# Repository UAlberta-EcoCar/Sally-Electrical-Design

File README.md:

# Branch for the original FOC-BOARD

Source code is located inside V1/FOC_SRC_V1
This is a CMake based project, and should be able to run in `STM32CubeIDE` or `STM32CubeIDE for VSCode`.

## Setup (If using Make)
1. Move inside V1/FOC_SRC_V1
```bash
cd V1/FOC_SRC_V1
```
2. Run the setup script
```bash
bash setup.sh
```
3. Run makefile to flash to device
```bash
make all
make flash
```

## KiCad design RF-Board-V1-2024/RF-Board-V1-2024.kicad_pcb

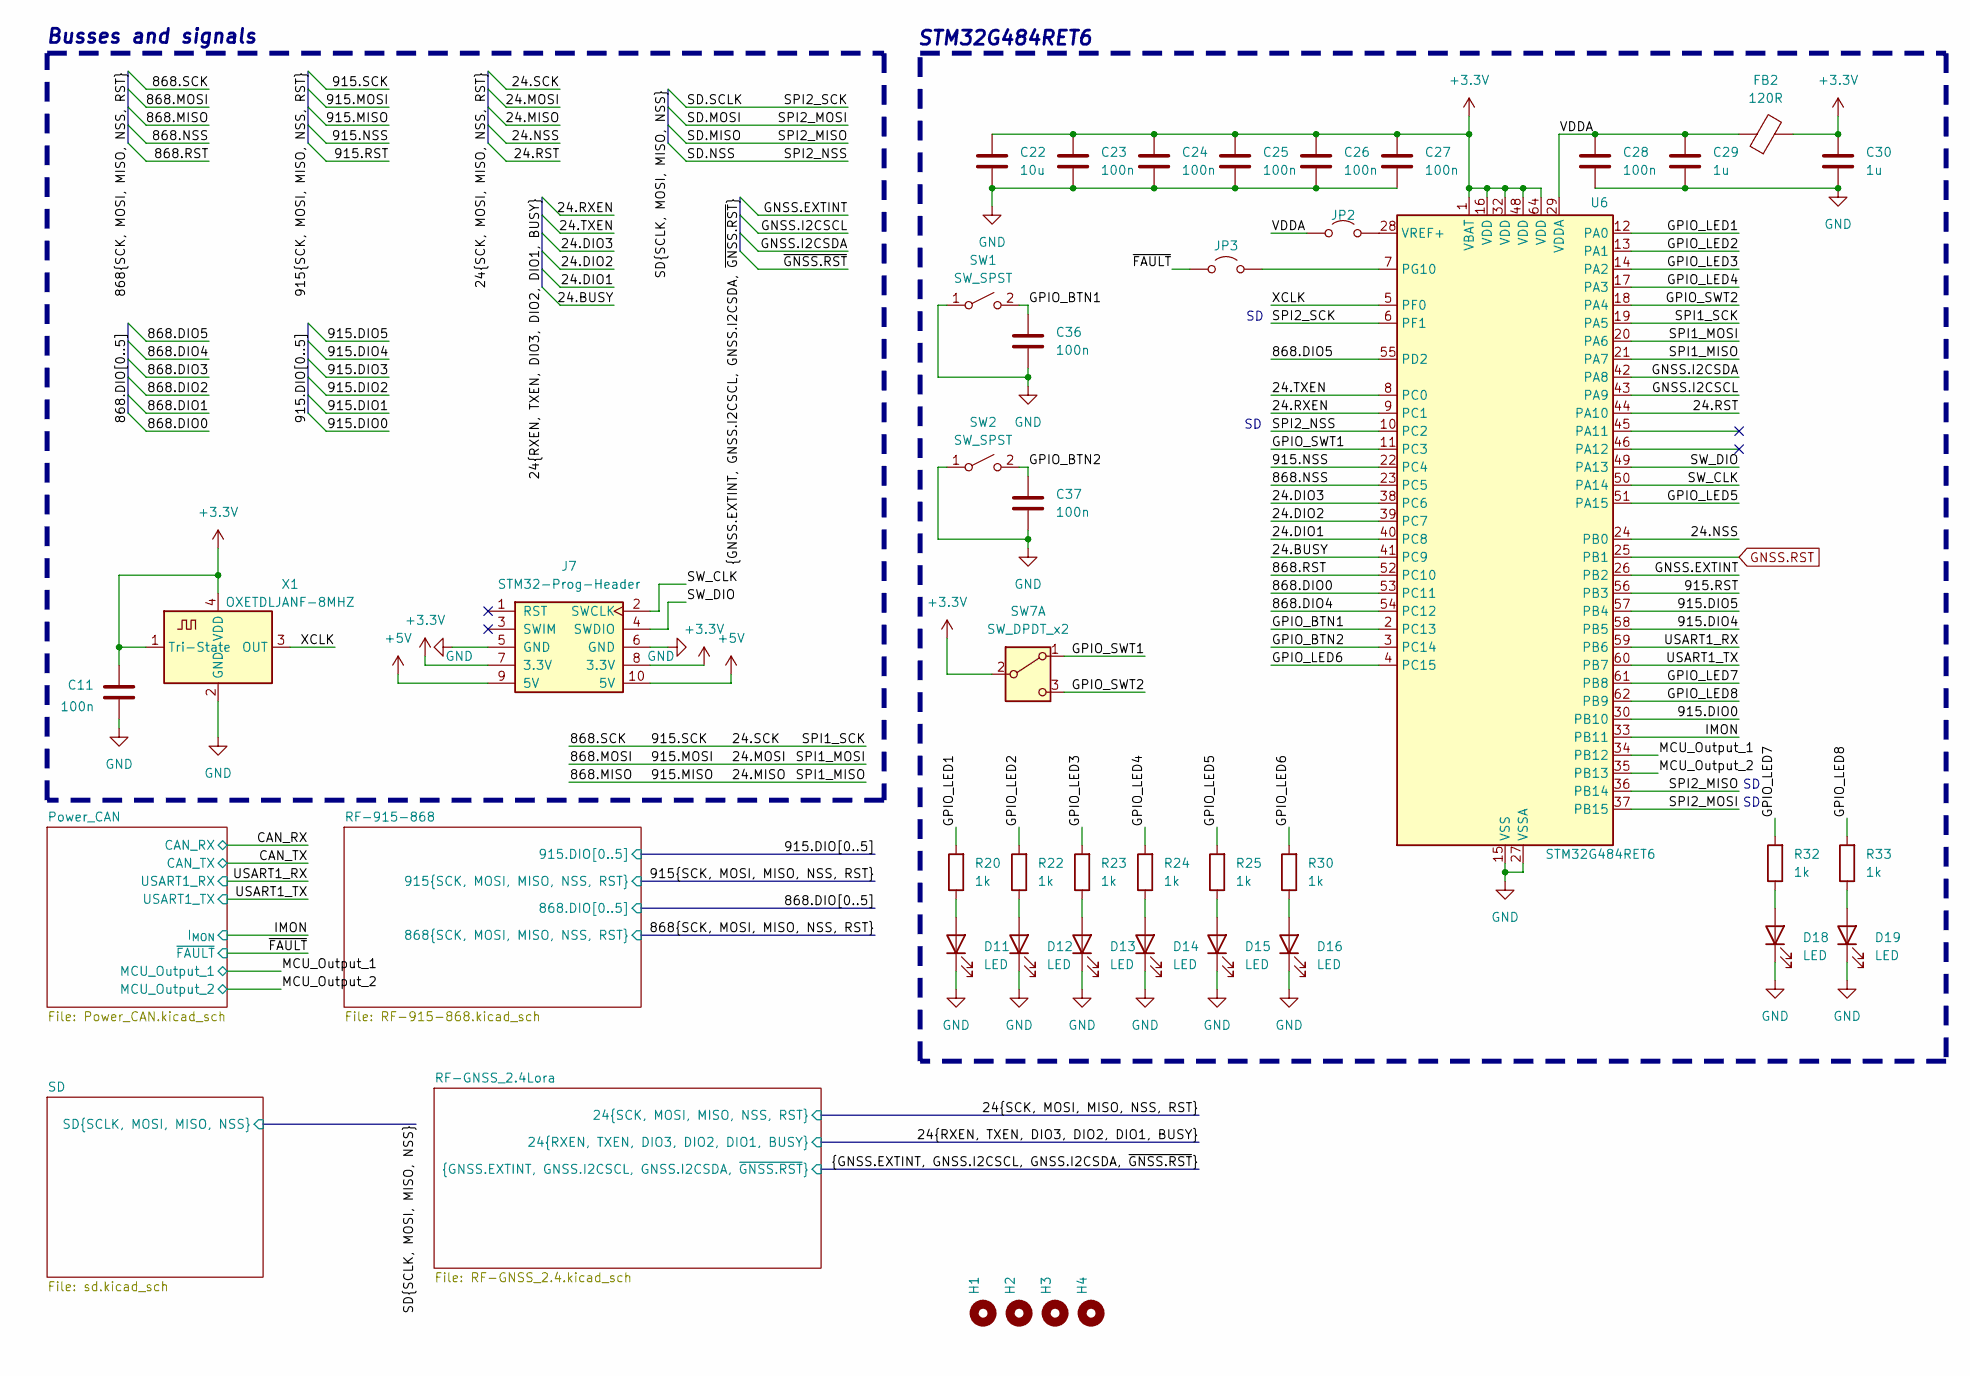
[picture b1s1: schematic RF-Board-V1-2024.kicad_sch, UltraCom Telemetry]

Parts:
C11, C23, C24, C25, C26, C27, C28, C36, C37: 100n; C_0805_2012Metric
C22: 10u; C_0805_2012Metric
C29, C30: 1u; C_0805_2012Metric
D11, D12, D13, D14, D15, D16, D18, D19: LED; LED_0603_1608Metric
FB2: 120R; R_0603_1608Metric
H1, H2, H3, H4: MountingHole_3.2mm_M3_Pad
J7: STM32-Prog-Header; IDC-STM32-Prog-Header_2x05_P2.54mm_Vertical
JP2, JP3: Jumper_2_Open; J_0603_Triangular
R20, R22, R23, R24, R25, R30, R32, R33: 1k; R_0603_1608Metric
SW1, SW2: SW_SPST; SW_PUSH_6mm
SW7: SW_DPDT_x2; SW_SPDT_PCM12
U6: STM32G484RET6; LQFP-64_10x10mm_P0.5mm
X1: OXETDLJANF-8MHZ; Crystal_SMD_3225-4Pin_3.2x2.5mm

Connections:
+5V: J7.9 (5V), J7.10 (5V); also elsewhere on the board
/24.BUSY: U6.41 (PC9); also elsewhere on the board
/24.DIO1: U6.40 (PC8); also elsewhere on the board
/24.DIO2: U6.39 (PC7); also elsewhere on the board
/24.DIO3: U6.38 (PC6); also elsewhere on the board
/24.MISO: U6.21 (PA7); also elsewhere on the board
/24.MOSI: U6.20 (PA6); also elsewhere on the board
/24.NSS: U6.24 (PB0); also elsewhere on the board
/24.RST: U6.44 (PA10); also elsewhere on the board
/24.RXEN: U6.9 (PC1); also elsewhere on the board
/24.SCK: U6.19 (PA5); also elsewhere on the board
/24.TXEN: U6.8 (PC0); also elsewhere on the board
/868.DIO0: U6.53 (PC11); also elsewhere on the board
/868.DIO4: U6.54 (PC12); also elsewhere on the board
/868.DIO5: U6.55 (PD2); also elsewhere on the board
/868.NSS: U6.23 (PC5); also elsewhere on the board
/868.RST: U6.52 (PC10); also elsewhere on the board
/915.DIO0: U6.30 (PB10); also elsewhere on the board
/915.DIO4: U6.58 (PB5); also elsewhere on the board
/915.DIO5: U6.57 (PB4); also elsewhere on the board
/915.NSS: U6.22 (PC4); also elsewhere on the board
/915.RST: U6.56 (PB3); also elsewhere on the board
/GNSS.EXTINT: U6.26 (PB2); also elsewhere on the board
/GNSS.I2CSCL: U6.43 (PA9); also elsewhere on the board
/GNSS.I2CSDA: U6.42 (PA8); also elsewhere on the board
/GPIO_BTN1: C36.1, SW1.2 (B), U6.2 (PC13)
/GPIO_BTN2: C37.1, SW2.2 (B), U6.3 (PC14)
/GPIO_LED1: R20.2, U6.12 (PA0)
/GPIO_LED2: R22.2, U6.13 (PA1)
/GPIO_LED3: R23.2, U6.14 (PA2)
/GPIO_LED4: R24.2, U6.17 (PA3)
/GPIO_LED5: R25.2, U6.51 (PA15)
/GPIO_LED6: R30.2, U6.4 (PC15)
/GPIO_LED7: R32.2, U6.61 (PB8)
/GPIO_LED8: R33.2, U6.62 (PB9)
/GPIO_SWT1: SW7.1 (A), U6.11 (PC3)
/GPIO_SWT2: SW7.3 (C), U6.18 (PA4)
/IMON: U6.33 (PB11); also elsewhere on the board
/MCU_Output_1: U6.34 (PB12); also elsewhere on the board
/MCU_Output_2: U6.35 (PB13); also elsewhere on the board
/SD.MISO: U6.36 (PB14); also elsewhere on the board
/SD.MOSI: U6.37 (PB15); also elsewhere on the board
/SD.NSS: U6.10 (PC2); also elsewhere on the board
/SD.SCLK: U6.6 (PF1); also elsewhere on the board
/SW_CLK: J7.2 (SWCLK), U6.50 (PA14)
/SW_DIO: J7.4 (SWDIO), U6.49 (PA13)
/USART1_RX: U6.59 (PB6)
/USART1_TX: U6.60 (PB7)
/VDDA: C28.1, C29.1, FB2.1, JP2.1 (A), U6.29 (VDDA)
/XCLK: U6.5 (PF0), X1.3 (OUT)
/~FAULT: JP3.1 (A); also elsewhere on the board
GND: C11.1, C22.2, C23.2, C24.2, C25.2, C26.2, C27.2, C28.2, C29.2, C30.2, C36.2, C37.2, D11.1 (K), D12.1 (K), D13.1 (K), D14.1 (K), D15.1 (K), D16.1 (K), D18.1 (K), D19.1 (K), J7.5 (GND), J7.6 (GND), SW1.1 (A), SW2.1 (A), U6.15 (VSS), U6.27 (VSSA), U6.31 (VSS), U6.47 (VSS), U6.63 (VSS), X1.2 (GND); also elsewhere on the board
GNSS.RST: U6.25 (PB1); also elsewhere on the board
unnamed: D11.2 (A), R20.1
unnamed: D12.2 (A), R22.1
unnamed: D13.2 (A), R23.1
unnamed: D14.2 (A), R24.1
unnamed: D15.2 (A), R25.1
unnamed: D16.2 (A), R30.1
unnamed: D18.2 (A), R32.1
unnamed: D19.2 (A), R33.1
unnamed: JP2.2 (B), U6.28 (VREF+)
unnamed: JP3.2 (B), U6.7 (PG10)

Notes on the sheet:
STM32G484RET6
Busses and signals

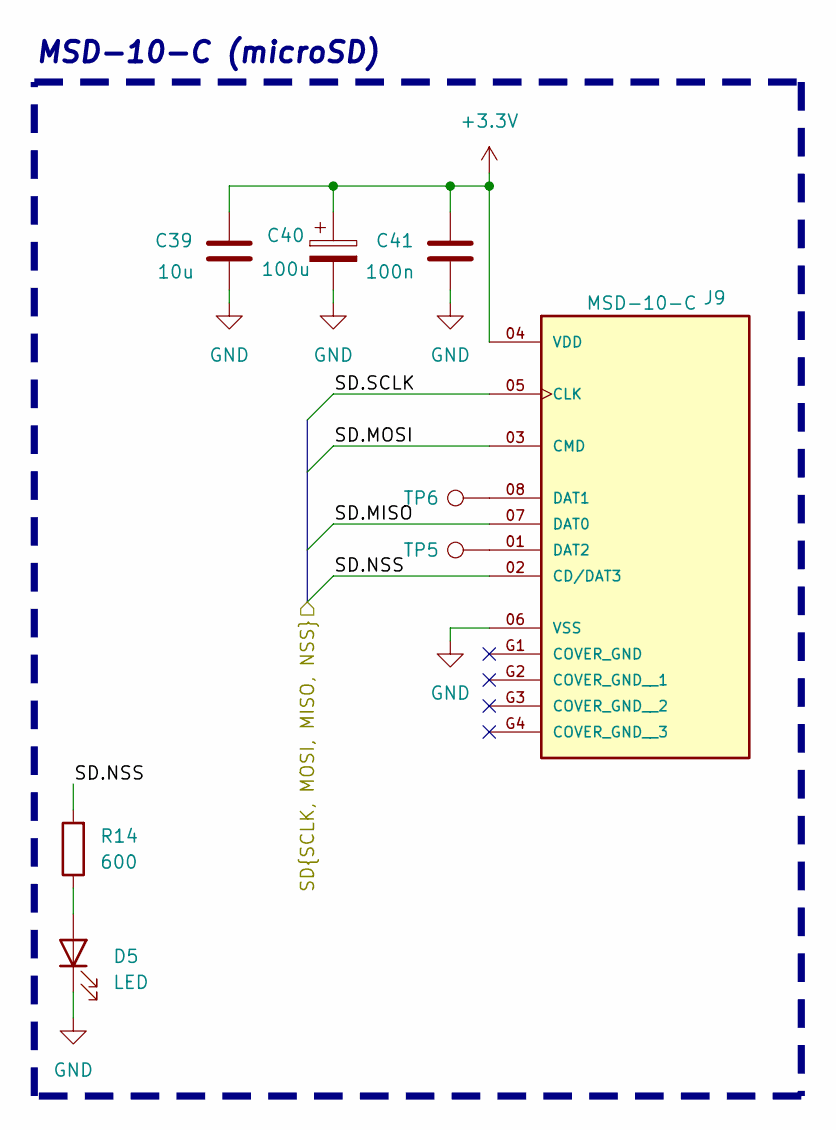
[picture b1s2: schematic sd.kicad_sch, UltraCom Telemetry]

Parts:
C39: 10u; C_0805_2012Metric
C40: 100u; CP_Elec_6.3x5.9
C41: 100n; C_0805_2012Metric
D5: LED; LED_0603_1608Metric
J9: MSD-10-C; CUI_MSD-10-C; PARTREV 1.0
R14: 600; R_0603_1608Metric
TP5, TP6: TestPoint; TestPoint_Pad_2.0x2.0mm

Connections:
/SD.MISO: J9.07 (DAT0); also elsewhere on the board
/SD.MOSI: J9.03 (CMD); also elsewhere on the board
/SD.NSS: J9.02 (CD/DAT3), R14.2; also elsewhere on the board
/SD.SCLK: J9.05 (CLK); also elsewhere on the board
GND: C39.1, C40.2, C41.1, D5.1 (K), J9.06 (VSS); also elsewhere on the board
unnamed: D5.2 (A), R14.1
unnamed: J9.08 (DAT1), TP6.1 (1_1)
unnamed: J9.01 (DAT2), TP5.1 (1_1)

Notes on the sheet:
MSD-10-C (microSD)

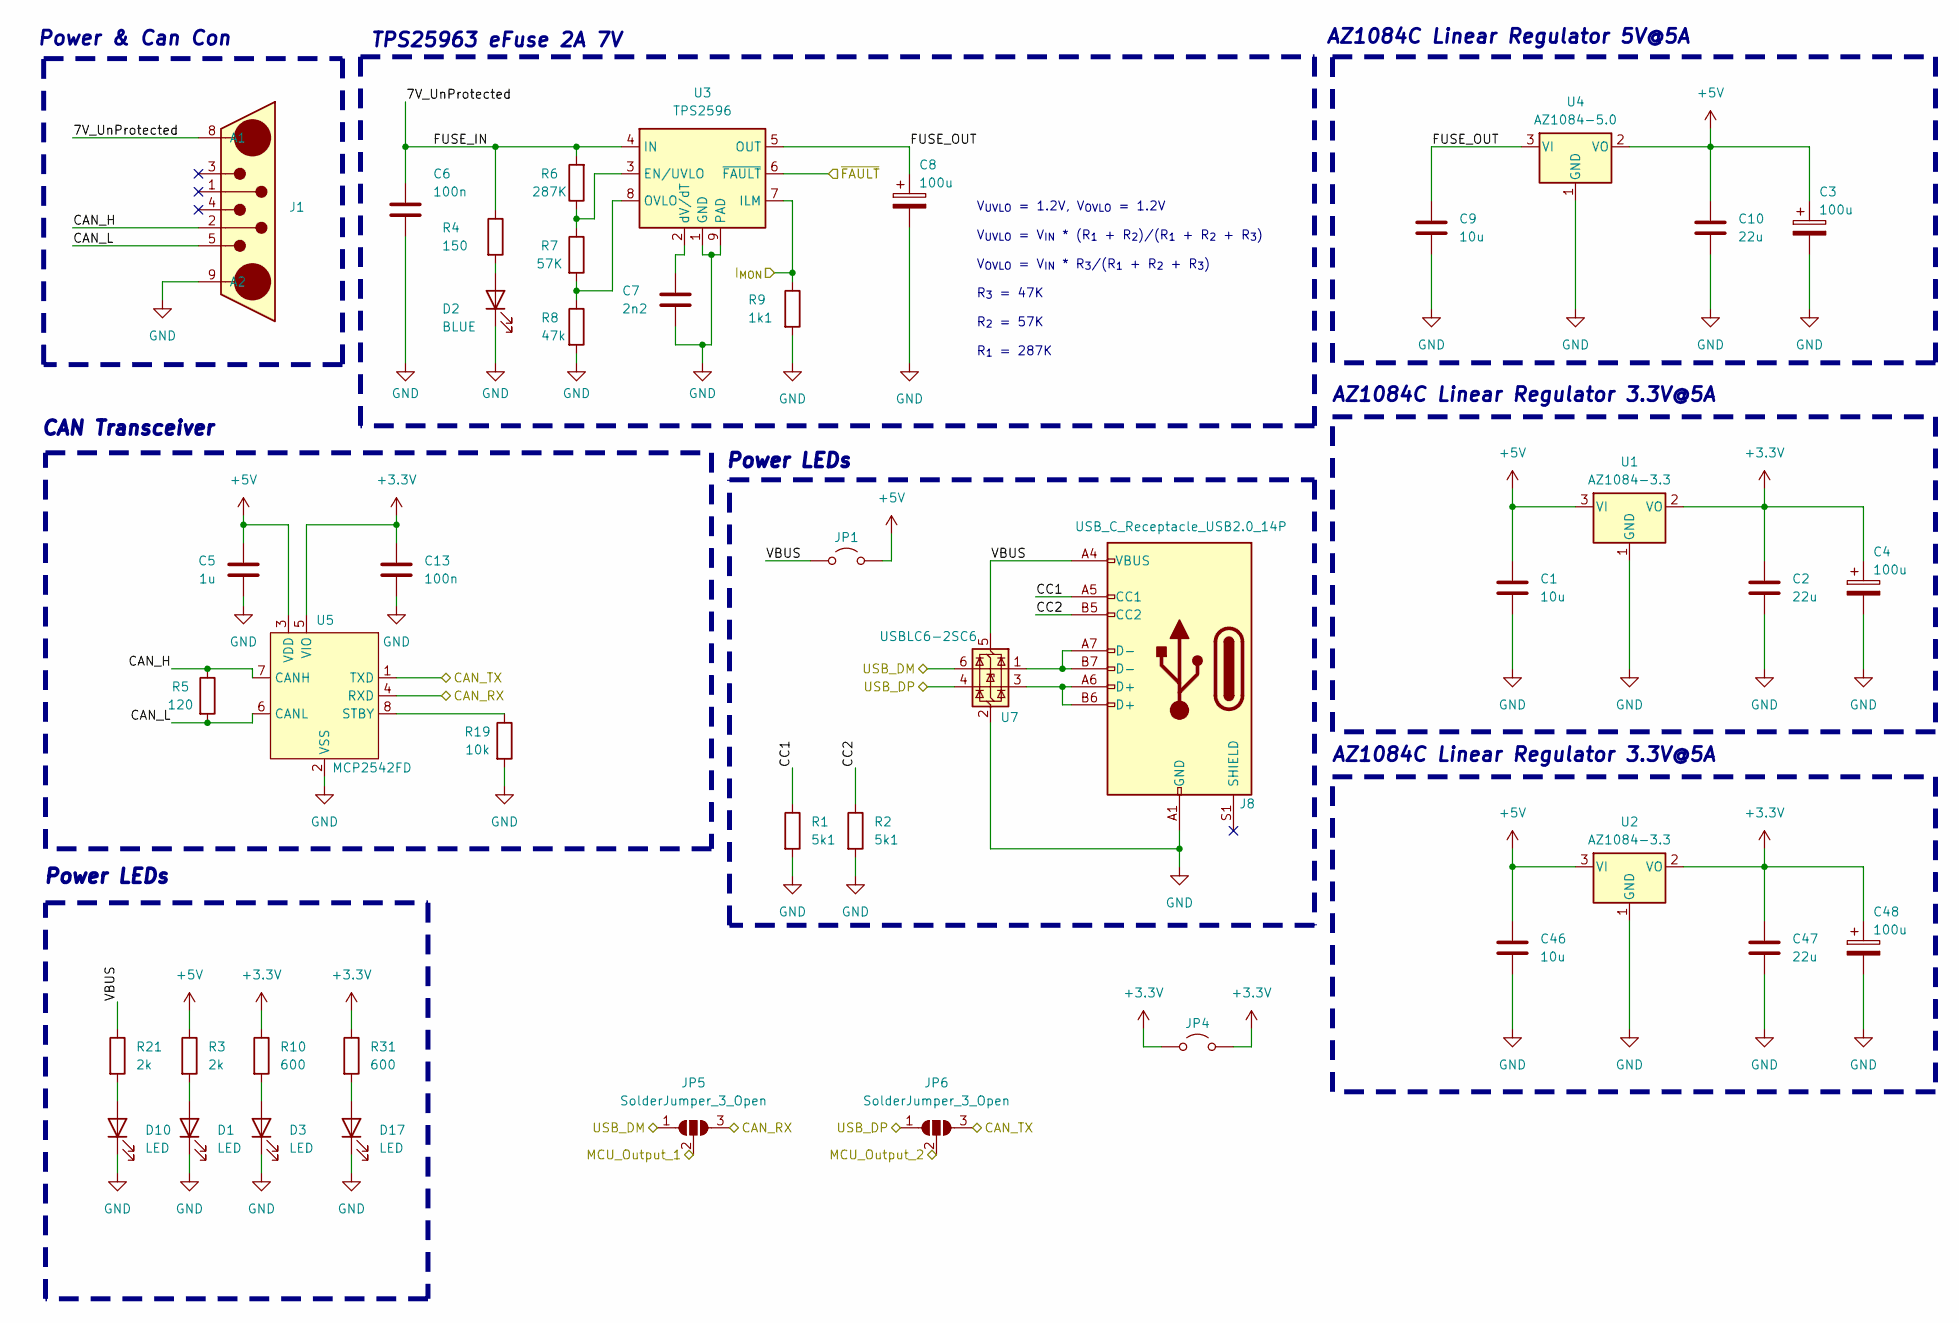
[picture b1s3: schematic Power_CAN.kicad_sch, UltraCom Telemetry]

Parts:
C1, C9, C46: 10u; C_0805_2012Metric
C2, C10, C47: 22u; C_0805_2012Metric
C3, C4, C8, C48: 100u; CP_Elec_6.3x5.9
C5: 1u; C_0805_2012Metric
C6: 100n; C_0805_2012Metric; JLCPCB Part#(optional) C14663
C7: 2n2; C_0805_2012Metric; JLCPCB Part#(optional) C1604
C13: 100n; C_0805_2012Metric
D1, D3, D10, D17: LED; LED_0603_1608Metric
D2: BLUE; LED_0603_1608Metric; JLCPCB Part#(optional) C72041
J1: DB7W2-Male
J8: USB_C_Receptacle_USB2.0_14P; USB_C_Receptacle_GCT_USB4105-xx-A_16P_TopMnt_Horizontal
JP1: Jumper_2_Open; J_0603_Triangular
JP4: Jumper_2_Open; Jumper_Micro-Miniature_P5.375mm
JP5, JP6: SolderJumper_3_Open; SolderJumper-3_P1.3mm_Open_RoundedPad1.0x1.5mm_NumberLabels
R1, R2: 5k1; R_0603_1608Metric
R3, R21: 2k; R_0603_1608Metric
R4: 150; R_0603_1608Metric; JLCPCB Part#(optional) C22808
R5: 120; R_0603_1608Metric
R6: 287K; R_0603_1608Metric; LCSC # C25815
R7: 57K; R_0603_1608Metric; LCSC # C170688
R8: 47k; R_0603_1608Metric; JLCPCB Part#(optional) C25819
R9: 1k1; R_0603_1608Metric; JLCPCB Part#(optional) C22764
R10, R31: 600; R_0603_1608Metric
R19: 10k; R_0603_1608Metric
U1, U2: AZ1084-3.3; TO-252-2
U3: TPS2596; TI_SO-PowerPAD-8
U4: AZ1084-5.0; TO-252-2
U5: MCP2542FD; SOIC-8_3.9x4.9mm_P1.27mm
U7: USBLC6-2SC6; SOT-23-6

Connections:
+5V: C1.1, C3.1, C5.1, C10.1, C46.1, JP1.2 (B), R3.1, U1.3 (VI), U2.3 (VI), U4.2 (VO), U5.3 (VDD); also elsewhere on the board
/CAN_RX: JP5.3 (B), U5.4 (RXD)
/CAN_TX: JP6.3 (B), U5.1 (TXD)
/IMON: R9.1, U3.7 (ILM); also elsewhere on the board
/MCU_Output_1: JP5.2 (C); also elsewhere on the board
/MCU_Output_2: JP6.2 (C); also elsewhere on the board
/Power_CAN/7V_UnProtected: C6.1, J1.8 (A1), R4.1, R6.2, U3.4 (IN)
/Power_CAN/CAN_H: J1.2, R5.1, U5.7 (CANH)
/Power_CAN/CAN_L: J1.5, R5.2, U5.6 (CANL)
/Power_CAN/CC1: J8.A5 (CC1), R1.1
/Power_CAN/CC2: J8.B5 (CC2), R2.1
/Power_CAN/FUSE_OUT: C8.1, C9.1, U3.5 (OUT), U4.3 (VI)
/Power_CAN/USB_DM: JP5.1 (A), U7.6 (I/O1)
/Power_CAN/USB_DP: JP6.1 (A), U7.4 (I/O2)
/Power_CAN/VBUS: J8.A4 (VBUS), J8.A9 (VBUS), J8.B4 (VBUS), J8.B9 (VBUS), JP1.1 (A), R21.1, U7.5 (VBUS)
/~FAULT: U3.6 (~FAULT); also elsewhere on the board
GND: C1.2, C2.2, C3.2, C4.2, C5.2, C6.2, C7.2, C8.2, C9.2, C10.2, C13.2, C46.2, C47.2, C48.2, D1.1 (K), D2.1 (K), D3.1 (K), D10.1 (K), D17.1 (K), J1.9 (A2), J8.A1 (GND), J8.A12 (GND), J8.B1 (GND), J8.B12 (GND), R1.2, R2.2, R8.2, R9.2, R19.2, U1.1 (GND), U2.1 (GND), U3.1 (GND), U3.9 (PAD), U4.1 (GND), U5.2 (VSS), U7.2 (GND); also elsewhere on the board
unnamed: D1.2 (A), R3.2
unnamed: D2.2 (A), R4.2
unnamed: D3.2 (A), R10.2
unnamed: D10.2 (A), R21.2
unnamed: D17.2 (A), R31.2
unnamed: J8.A6 (D+), J8.B6 (D+), U7.3 (I/O2)
unnamed: J8.A7 (D-), J8.B7 (D-), U7.1 (I/O1)
unnamed: R6.1, R7.1, U3.3 (EN/UVLO)
unnamed: R7.2, R8.1, U3.8 (OVLO)
unnamed: C7.1, U3.2 (dV/dT)
unnamed: R19.1, U5.8 (STBY)

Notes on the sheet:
AZ1084C Linear Regulator 5V@5A
CAN Transceiver
V_{UVLO} = 1.2V, V_{OVLO} = 1.2V V_{UVLO} = V_{IN} * (R_{1} + R_{2})/(R_{1} + R_{2} + R_{3}) V_{OVLO} = V_{IN} * R_{3}/(R_{1} + R_{2} + R_{3}) R_{3} = 47K R_{2} = 57K R_{1} = 287K
Power & Can Con
AZ1084C Linear Regulator 3.3V@5A
TPS25963 eFuse 2A 7V
Power LEDs

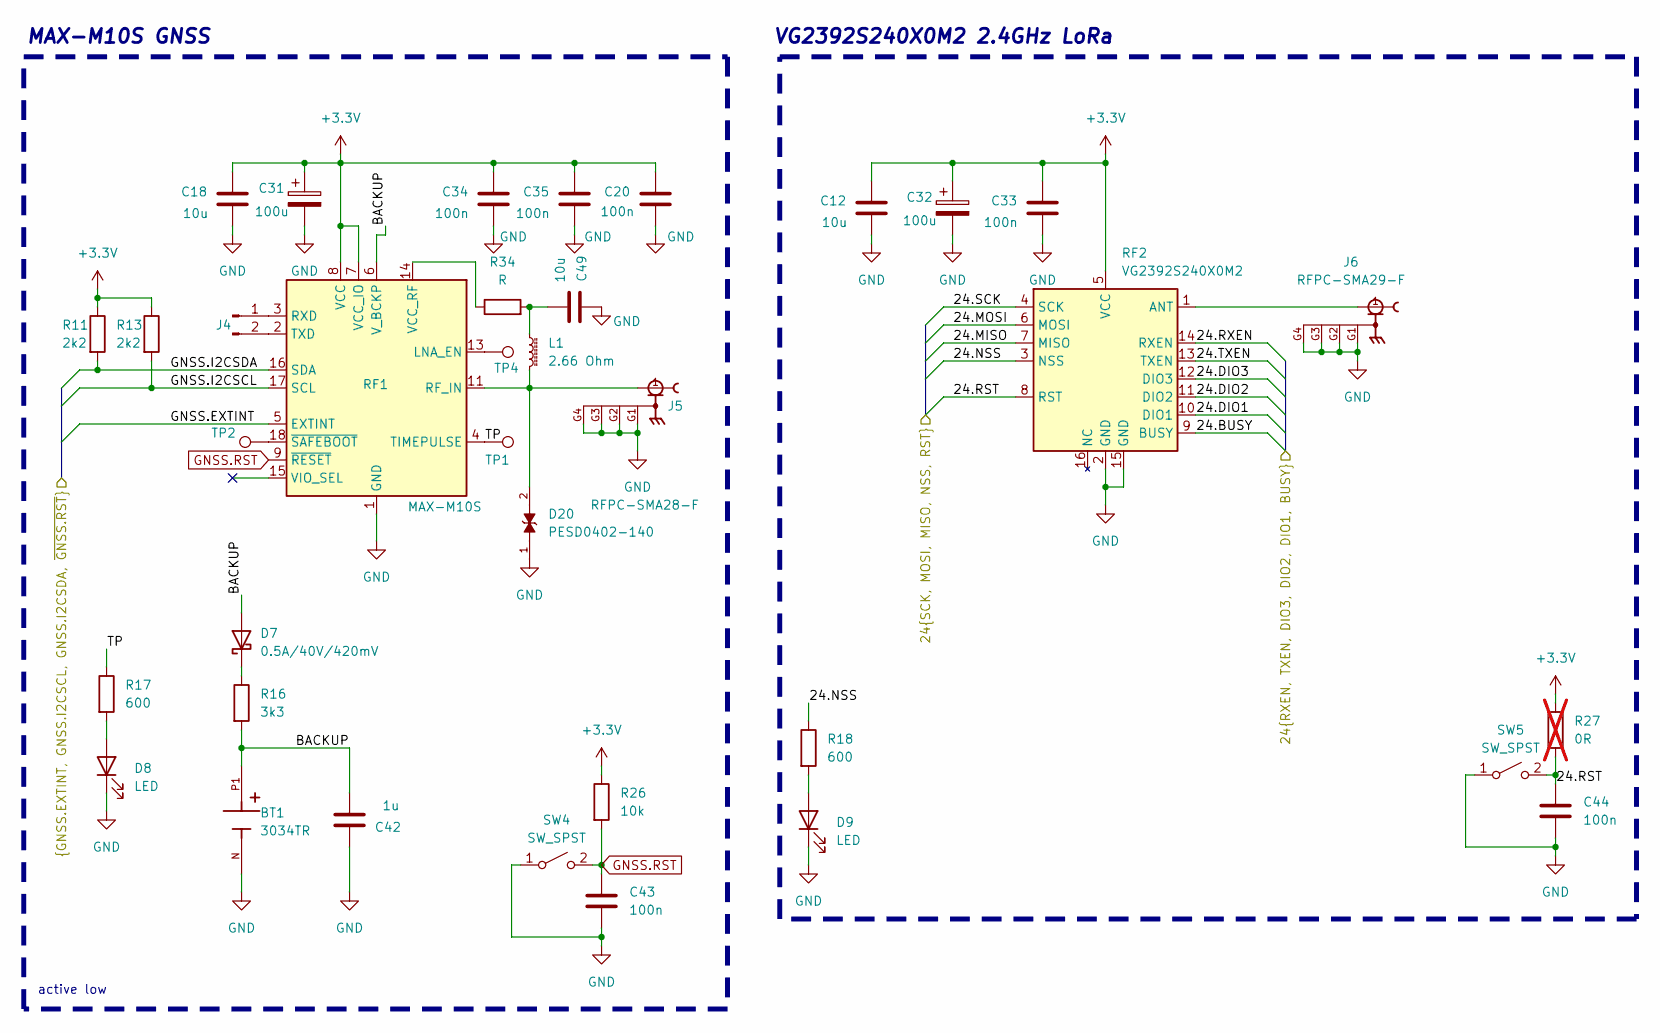
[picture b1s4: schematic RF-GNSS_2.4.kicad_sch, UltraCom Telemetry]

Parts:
BT1: 3034TR; BAT_3034TR; PARTREV E
C12, C18, C49: 10u; C_0805_2012Metric
C20, C33, C34, C35, C43, C44: 100n; C_0805_2012Metric
C31, C32: 100u; CP_Elec_6.3x5.9
C42: 1u; C_0805_2012Metric
D7: 0.5A/40V/420mV; D_SOD-123
D8, D9: LED; LED_0603_1608Metric
D20: PESD0402-140; DIO_PESD0402-140; PARTREV 2016
J4: UART; PinHeader_1x02_P2.54mm_Vertical
J5: RFPC-SMA28-F; GRADCONN_RFPC-SMA28-F; PARTREV 1.0
J6: RFPC-SMA29-F; GRADCONN_RFPC-SMA29-F; PARTREV 1.0
L1: 2.66 Ohm; R_0603_1608Metric
R11, R13: 2k2; R_0603_1608Metric; JLCPCB Part#(optional) C25819
R16: 3k3; R_0603_1608Metric
R17, R18: 600; R_0603_1608Metric
R26: 10k; R_0603_1608Metric
R27: 0R; R_0603_1608Metric; not fitted
R34: R; R_0201_0603Metric
RF1: MAX-M10S; ublox_MAX
RF2: VG2392S240X0M2; Vollgo VG2392S240X0M2; LCSC # C2976523
SW4, SW5: SW_SPST; SW_PUSH_6mm
TP1, TP2, TP4: TestPoint; TestPoint_Pad_2.0x2.0mm

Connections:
/24.BUSY: RF2.9 (BUSY); also elsewhere on the board
/24.DIO1: RF2.10 (DIO1); also elsewhere on the board
/24.DIO2: RF2.11 (DIO2); also elsewhere on the board
/24.DIO3: RF2.12 (DIO3); also elsewhere on the board
/24.MISO: RF2.7 (MISO); also elsewhere on the board
/24.MOSI: RF2.6 (MOSI); also elsewhere on the board
/24.NSS: R18.1, RF2.3 (NSS); also elsewhere on the board
/24.RST: C44.1, R27.2, RF2.8 (RST), SW5.2 (B); also elsewhere on the board
/24.RXEN: RF2.14 (RXEN); also elsewhere on the board
/24.SCK: RF2.4 (SCK); also elsewhere on the board
/24.TXEN: RF2.13 (TXEN); also elsewhere on the board
/GNSS.EXTINT: RF1.5 (EXTINT); also elsewhere on the board
/GNSS.I2CSCL: R13.2, RF1.17 (SCL); also elsewhere on the board
/GNSS.I2CSDA: R11.2, RF1.16 (SDA); also elsewhere on the board
/RF-GNSS_2.4Lora/TP: R17.1, RF1.4 (TIMEPULSE), TP1.1 (1_1)
GND: BT1.N, C12.1, C18.1, C20.1, C31.2, C32.2, C33.1, C34.1, C35.1, C42.2, C43.2, C44.2, C49.2, D8.1 (K), D9.1 (K), D20.1, J5.G1, J5.G2, J5.G3, J5.G4, J6.G1, J6.G2, J6.G3, J6.G4, RF1.1 (GND), RF1.10 (GND), RF1.12 (GND), RF2.2 (GND), RF2.15 (GND), SW4.1 (A), SW5.1 (A); also elsewhere on the board
GNSS.RST: C43.1, R26.2, RF1.9 (~RESET), SW4.2 (B); also elsewhere on the board
unnamed: C49.1, L1.1, R34.2
unnamed: D7.1 (K), R16.1
unnamed: D8.2 (A), R17.2
unnamed: D9.2 (A), R18.2
unnamed: J4.1, RF1.3 (RXD)
unnamed: J4.2, RF1.2 (TXD)
unnamed: RF1.13 (LNA_EN), TP4.1 (1_1)
unnamed: D20.2, J5.1, L1.2, RF1.11 (RF_IN)
unnamed: R34.1, RF1.14 (VCC_RF)
unnamed: RF1.18 (~SAFEBOOT), TP2.1 (1_1)
unnamed: J6.1, RF2.1 (ANT)

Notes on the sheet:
MAX-M10S GNSS
active low
VG2392S240X0M2 2.4GHz LoRa

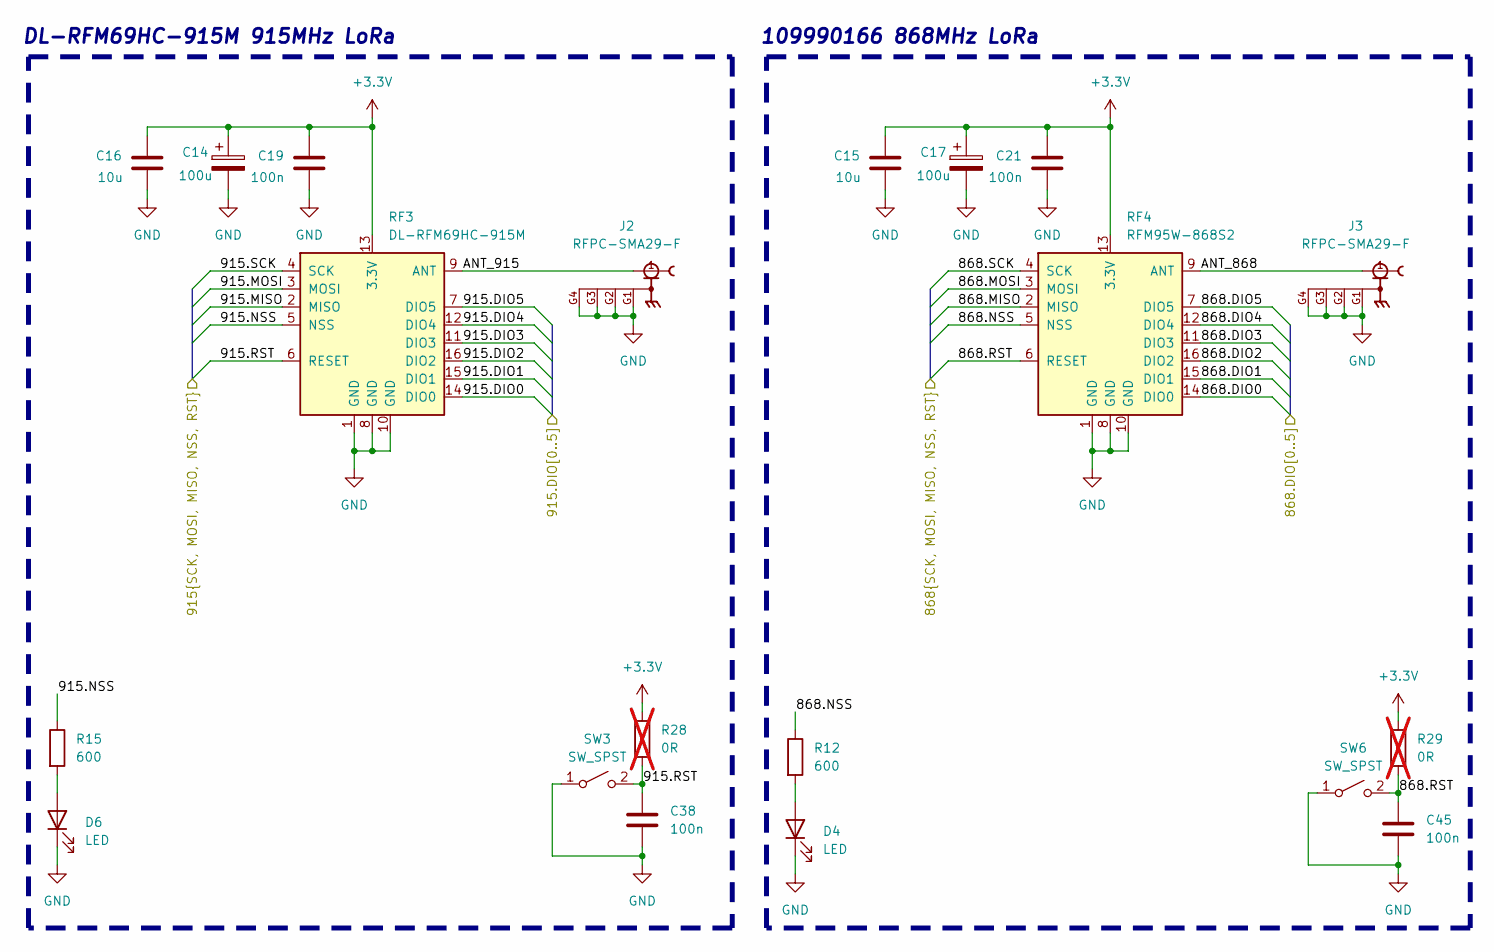
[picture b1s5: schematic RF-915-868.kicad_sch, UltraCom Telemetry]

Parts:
C14, C17: 100u; CP_Elec_6.3x5.9
C15, C16: 10u; C_0805_2012Metric
C19, C21, C38, C45: 100n; C_0805_2012Metric
D4, D6: LED; LED_0603_1608Metric
J2, J3: RFPC-SMA29-F; GRADCONN_RFPC-SMA29-F; PARTREV 1.0
R12, R15: 600; R_0603_1608Metric
R28, R29: 0R; R_0603_1608Metric; not fitted
RF3: DL-RFM69HC-915M; HOPERF_RFM9XW_SMD; LCSC # C2844478
RF4: RFM95W-868S2; HOPERF_RFM9XW_SMD
SW3, SW6: SW_SPST; SW_PUSH_6mm

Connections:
/24.MISO: RF3.2 (MISO), RF4.2 (MISO); also elsewhere on the board
/24.MOSI: RF3.3 (MOSI), RF4.3 (MOSI); also elsewhere on the board
/24.SCK: RF3.4 (SCK), RF4.4 (SCK); also elsewhere on the board
/868.DIO0: RF4.14 (DIO0); also elsewhere on the board
/868.DIO1: RF4.15 (DIO1)
/868.DIO2: RF4.16 (DIO2)
/868.DIO3: RF4.11 (DIO3)
/868.DIO4: RF4.12 (DIO4); also elsewhere on the board
/868.DIO5: RF4.7 (DIO5); also elsewhere on the board
/868.NSS: R12.1, RF4.5 (NSS); also elsewhere on the board
/868.RST: C45.1, R29.2, RF4.6 (RESET), SW6.2 (B); also elsewhere on the board
/915.DIO0: RF3.14 (DIO0); also elsewhere on the board
/915.DIO1: RF3.15 (DIO1)
/915.DIO2: RF3.16 (DIO2)
/915.DIO3: RF3.11 (DIO3)
/915.DIO4: RF3.12 (DIO4); also elsewhere on the board
/915.DIO5: RF3.7 (DIO5); also elsewhere on the board
/915.NSS: R15.1, RF3.5 (NSS); also elsewhere on the board
/915.RST: C38.1, R28.2, RF3.6 (RESET), SW3.2 (B); also elsewhere on the board
/RF-915-868/ANT_868: J3.1, RF4.9 (ANT)
/RF-915-868/ANT_915: J2.1, RF3.9 (ANT)
GND: C14.2, C15.1, C16.1, C17.2, C19.1, C21.1, C38.2, C45.2, D4.1 (K), D6.1 (K), J2.G1, J2.G2, J2.G3, J2.G4, J3.G1, J3.G2, J3.G3, J3.G4, RF3.1 (GND), RF3.8 (GND), RF3.10 (GND), RF4.1 (GND), RF4.8 (GND), RF4.10 (GND), SW3.1 (A), SW6.1 (A); also elsewhere on the board
unnamed: D4.2 (A), R12.2
unnamed: D6.2 (A), R15.2

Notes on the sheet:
DL-RFM69HC-915M 915MHz LoRa
109990166 868MHz LoRa

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
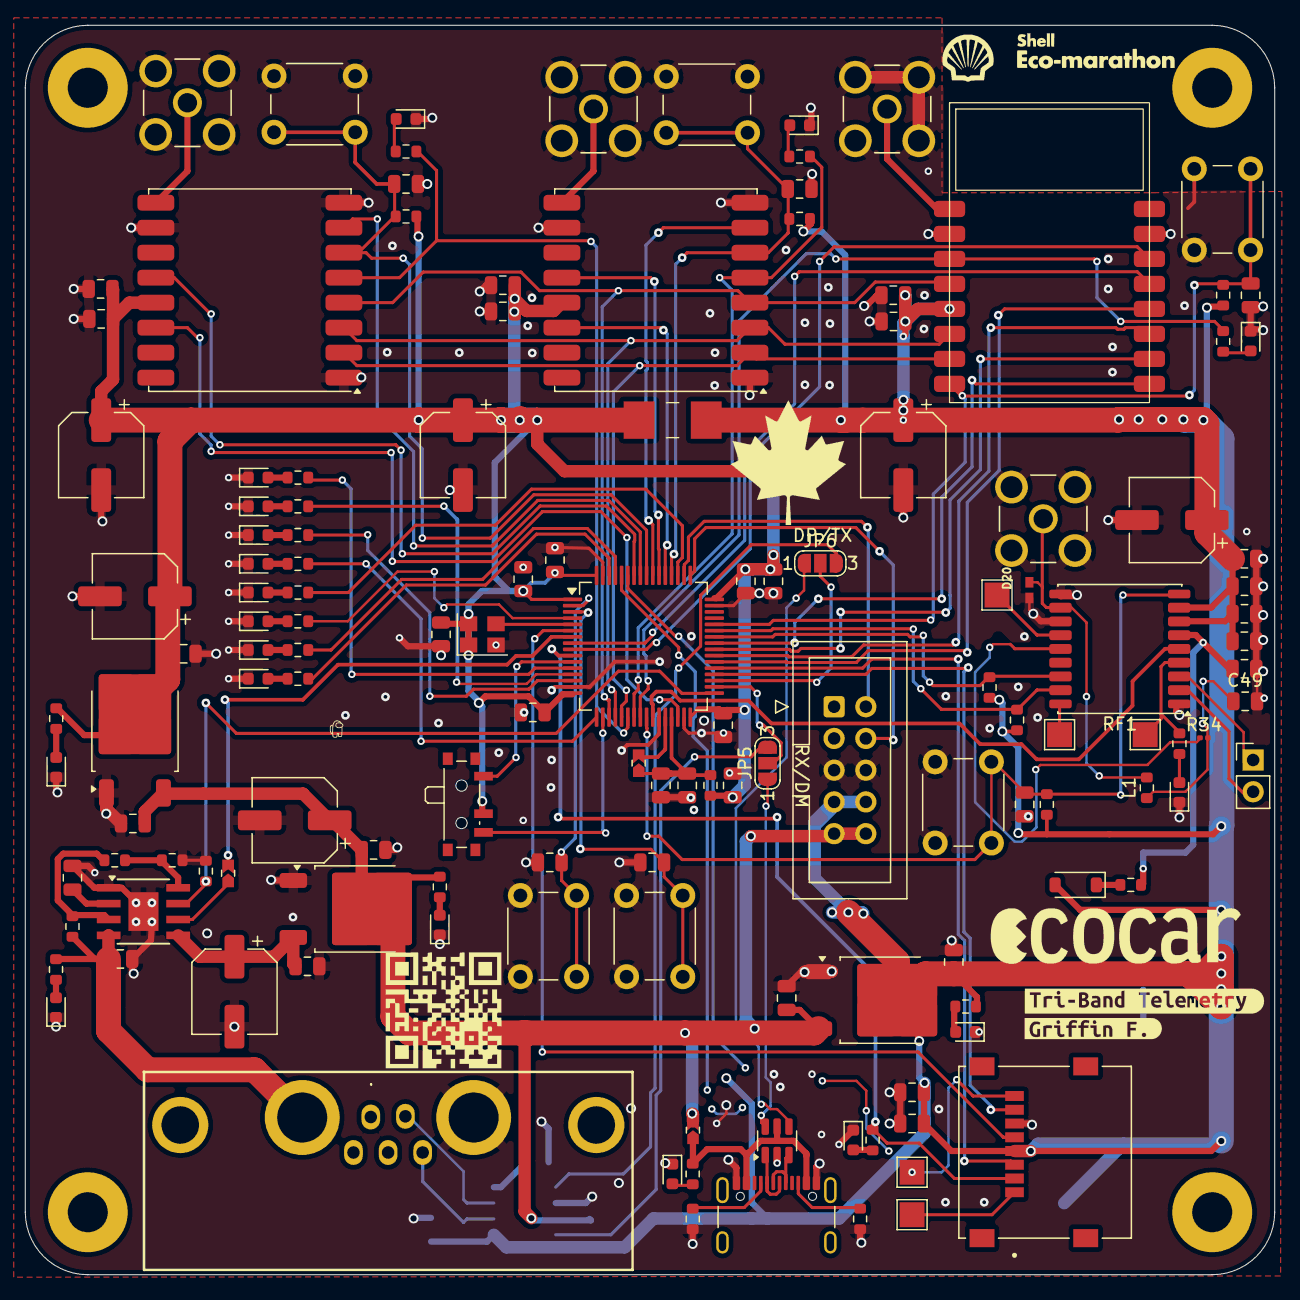
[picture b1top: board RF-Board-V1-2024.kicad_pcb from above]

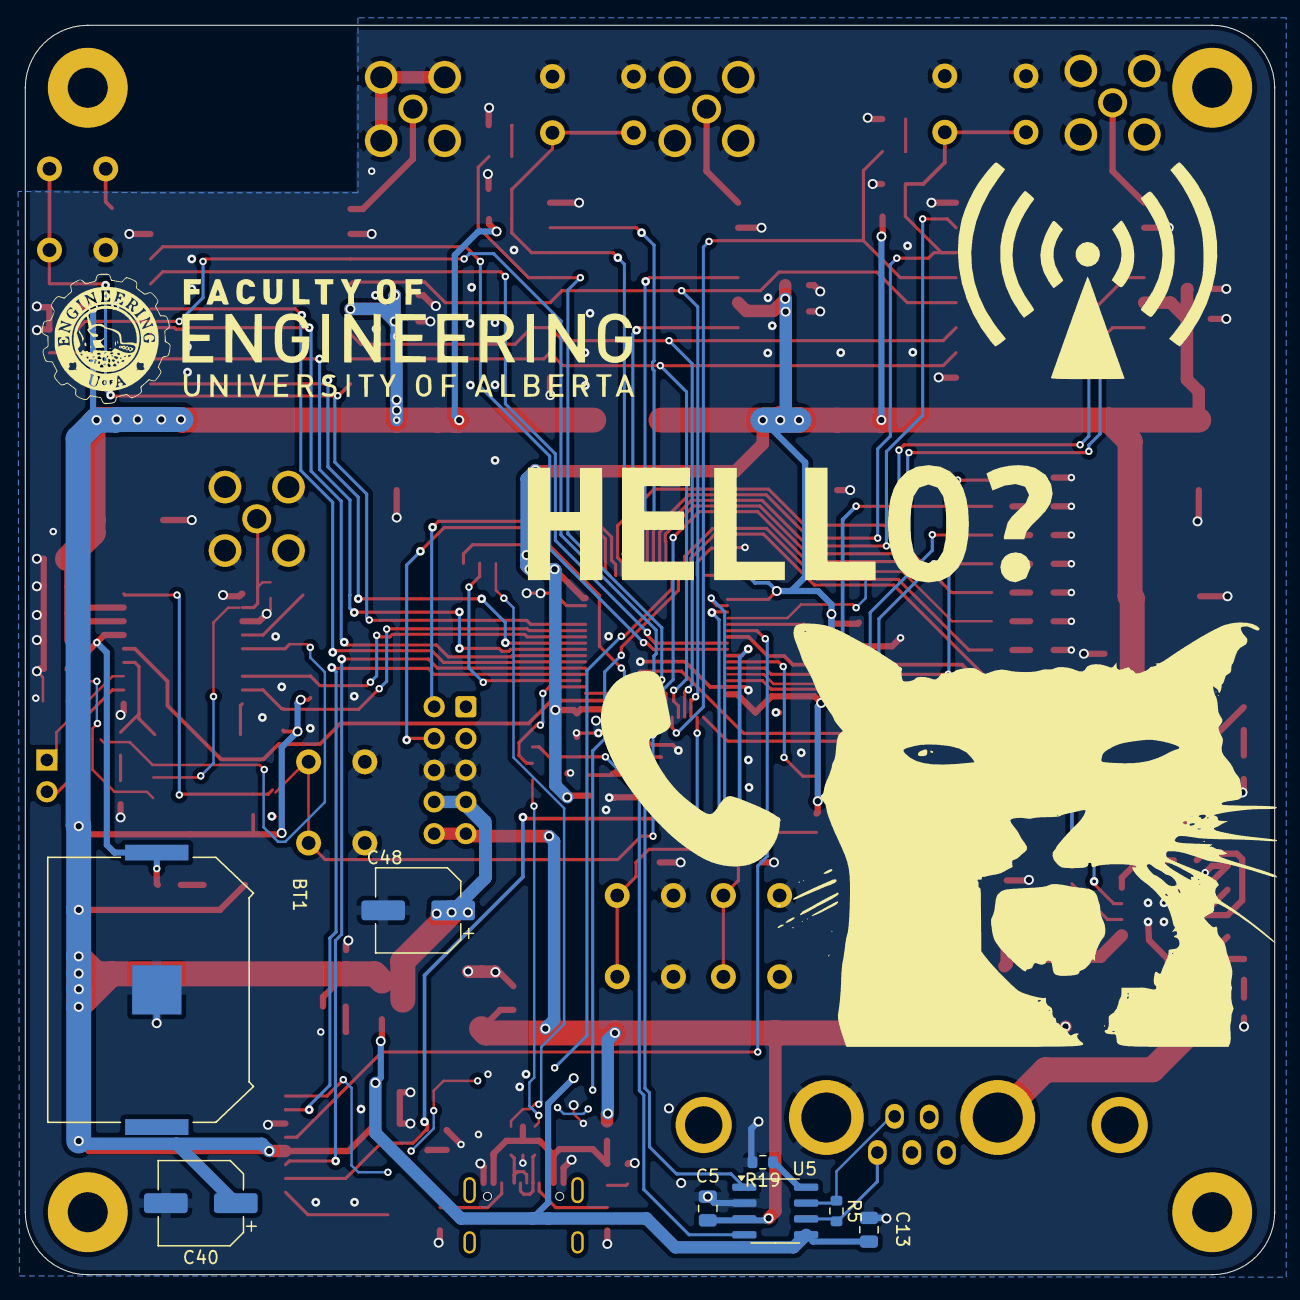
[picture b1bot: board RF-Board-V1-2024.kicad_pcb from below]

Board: 2 copper layers, 100.0 x 100.0 mm, 152 parts (9 on the bottom side), 104 nets.

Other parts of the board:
kibuzzard-679868A6: G***; kibuzzard-679868A6
kibuzzard-6798610B: G***; kibuzzard-6798610B
kibuzzard-6798611E: G***; kibuzzard-6798611E

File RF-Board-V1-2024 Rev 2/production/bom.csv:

Designator,Footprint,Quantity,Value,LCSC Part #
BT1,BAT_3034TR,1,3034TR,
"C1, C12, C15, C16, C18, C22, C39, C46, C9",0805,9,10u,
"C10, C2, C47",0805,3,22u,
"C11, C13, C19, C20, C21, C23, C24, C25, C26, C27, C28, C33, C34, C35, C36, C37, C38, C41, C43, C44, C45, C49, C50, C53, C6",0805,25,100n,
"C14, C17, C3, C31, C32, C4, C40, C48, C8",CP_Elec_6.3x5.9,9,100u,
"C29, C30, C42, C5",0805,4,1u,
"C51, C52",0603,2,47p,
C7,0805,1,2n2,
"D1, D10, D11, D12, D13, D14, D15, D16, D17, D18, D19, D20, D3, D4, D5, D6, D8, D9",0603,18,LED,
D2,0603,1,BLUE,
D7,D_SOD-123,1,0.5A/40V/420mV,
FB2,0603,1,120R,
"H1, H2, H3, H4",MountingHole_3.2mm_M3_Pad,4,~,
J1,DB7W2-Male,1,~,
"J2, J3, J6",GRADCONN_RFPC-SMA29-F,3,RFPC-SMA29-F,
J4,PinHeader_1x02_P2.54mm_Vertical,1,UART,
J5,GRADCONN_RFPC-SMA28-F,1,RFPC-SMA28-F,
J7,IDC-STM32-Prog-Header_2x05_P2.54mm_Vertical,1,STM32-Prog-Header,
J8,USB_C_Receptacle_GCT_USB4105-xx-A_16P_TopMnt_Horizontal,1,USB_C_Receptacle_USB2.0_14P,
J9,CUI_MSD-10-C,1,MSD-10-C,
"JP1, JP2",J_0603_Triangular,2,Jumper_2_Open,
JP4,Jumper_Micro-Miniature_P5.375mm,1,Jumper_2_Open,
"R1, R2",0603,2,5k1,
"R10, R12, R14, R15, R17, R18, R31, R34",0603,8,600,
"R11, R13",0603,2,2k2,
R16,0603,1,3k3,
"R19, R26",0603,2,10k,
"R20, R22, R23, R24, R25, R30, R32, R33, R37",0603,9,1k,
"R21, R3",0603,2,2k,
"R27, R28, R29",0603,3,0R,
"R35, R36",0603,2,27R,
R4,0603,1,150,
R5,0603,1,120,
R6,0603,1,287K,
R7,0603,1,57K,
R8,0603,1,47k,
R9,0603,1,1k1,
RF1,ublox_MAX,1,MAX-M10S,
RF2,Vollgo VG2392S240X0M2,1,VG2392S240X0M2,
RF3,HOPERF_RFM9XW_SMD,1,DL-RFM69HC-915M,
RF4,HOPERF_RFM9XW_SMD,1,RFM95W-868S2,
"SW1, SW2, SW3, SW4, SW5, SW6, SW8",SW_PUSH_6mm,7,SW_SPST,
SW7,SW_SPDT_PCM12,1,SW_DPDT_x2,
"TP1, TP2, TP3, TP4, TP5, TP6",TestPoint_Pad_2.0x2.0mm,6,TestPoint,
"U1, U2",TO-252-2,2,AZ1084-3.3,
U3,TI_SO-PowerPAD-8,1,TPS2596,
U4,TO-252-2,1,AZ1084-5.0,
U5,SOIC-8_3.9x4.9mm_P1.27mm,1,MCP2542FD,
U6,LQFP-64_10x10mm_P0.5mm,1,STM32G484RET6,
U7,SOT-23-6,1,USBLC6-2SC6,
U8,DFN-12-1EP_3x3mm,1,FT234XD-R,FT234XD-R
X1,Crystal_SMD_3225-4Pin_3.2x2.5mm,1,OXETDLJANF-8MHZ,
